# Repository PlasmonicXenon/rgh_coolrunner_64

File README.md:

# RGH_Coolrunner_64
This is an approximate replica of the coolrunner rev C based on the clones I 
have, but with a few extra features.

The extra features include solder points for level shifting post, an extra pll
io pad, as well as a crowbar point and a nand chip enable point for a potential
future Oban voltage glitch, if that ever happens and is ported to the xc2c64.

Note that the post points do not exactly match the configuration Octal450's 
level_shifter uses, which isn't a problem for my usecase.  If one wants to
use level_shifter, either edit the UCF file or wire to match it.

As mentioned above, this pcb has two IO pads that can drive the PLL point -- the
usual 3v3 io pad through a 22k resistor as usual, and an IO pad in the CPU VCCIO
bank. This second pad is only intended to be used with slims because the 
coolrunner  II's lowest IO voltage is 1.5V whereas phat CPUs use V_GPUCORE 
(~1.1 V) as their  IO voltage.  The intent here is that driving PLL_BYPASS with
a lower impedance should reduce its sensitivity to interference.

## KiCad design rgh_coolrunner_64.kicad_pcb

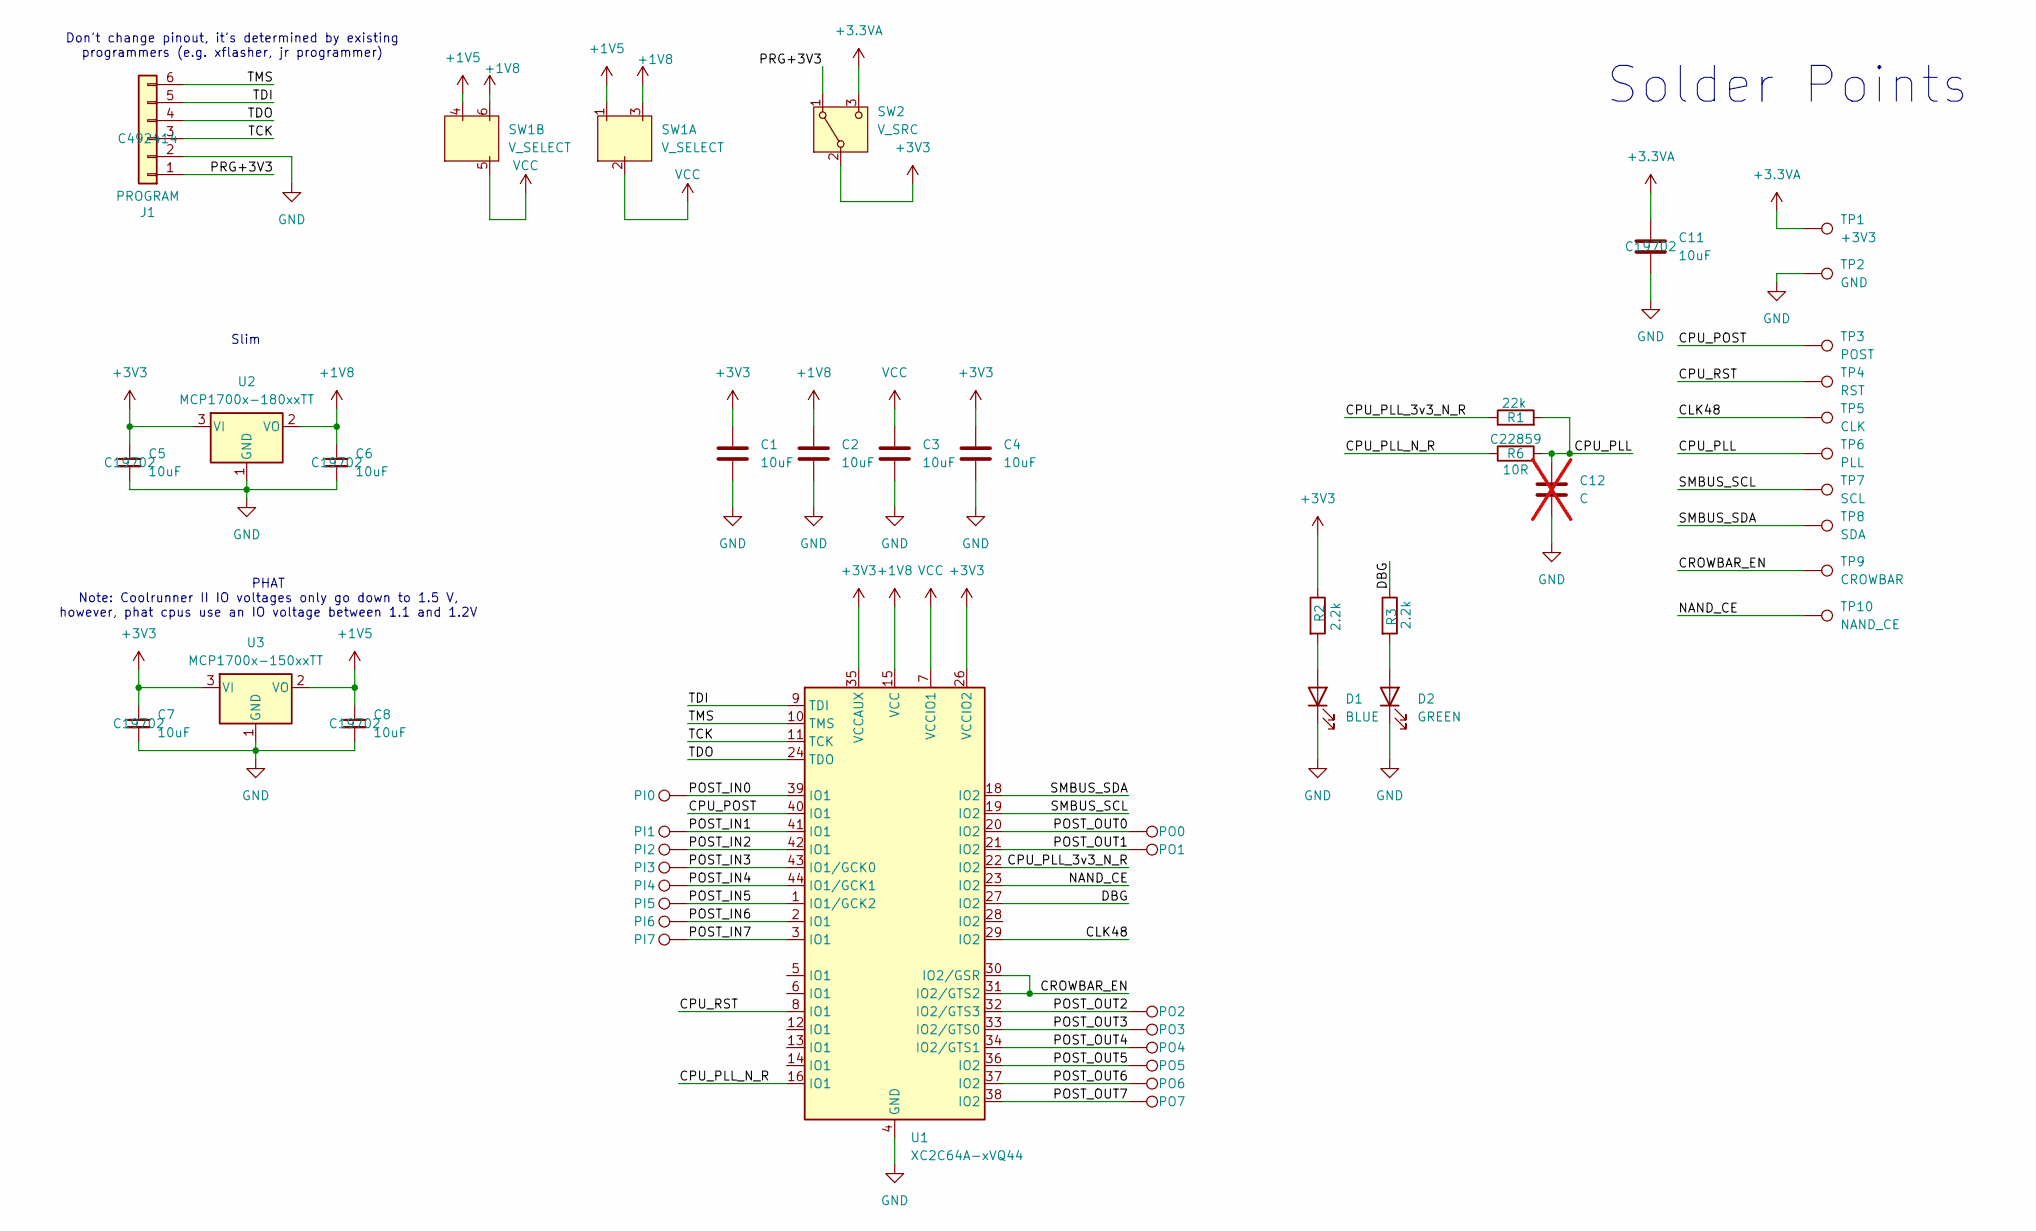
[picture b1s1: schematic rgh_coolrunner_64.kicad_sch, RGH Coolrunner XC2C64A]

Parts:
C1, C2, C3, C4: 10uF; C_0603_1608Metric
C5, C6, C7, C8, C11: 10uF; C_0603_1608Metric; LCSC Part # C19702
C12: C; C_0805_2012Metric_Pad1.18x1.45mm_HandSolder; not fitted
D1: BLUE; LED_0603_1608Metric; LCSC Part # C965807
D2: GREEN; LED_0603_1608Metric
J1: PROGRAM; PinHeader_1x06_P2.54mm_Horizontal; LCSC Part # C492414
PI0, PI1, PI2, PI3, PI4, PI5, PI6, PI7: TestPoint; TestPoint_Pad_D1.0mm
PO0, PO1, PO2, PO3, PO4, PO5, PO6, PO7: TestPoint; TestPoint_Pad_D1.0mm
R1: 22k; R_0603_1608Metric_Pad0.98x0.95mm_HandSolder
R2, R3: 2.2k; R_0603_1608Metric
R6: 10R; R_0603_1608Metric_Pad0.98x0.95mm_HandSolder; LCSC Part # C22859
SW1: V_SELECT; SW_DPDT_CK_JS202011JCQN
SW2: V_SRC; SW_SPDT_PCM12
TP1: +3V3; TestPoint_Pad_D2.0mm
TP2: GND; TestPoint_Pad_D2.0mm
TP3: POST; TestPoint_Pad_D2.0mm
TP4: RST; TestPoint_Pad_D2.0mm
TP5: CLK; TestPoint_Pad_D2.0mm
TP6: PLL; TestPoint_Pad_D2.0mm
TP7: SCL; TestPoint_Pad_D2.0mm
TP8: SDA; TestPoint_Pad_D2.0mm
TP9: CROWBAR; TestPoint_Pad_D2.0mm
TP10: NAND_CE; TestPoint_Pad_D2.0mm
U1: XC2C64A-xVQ44; TQFP-44_10x10mm_P0.8mm
U2: MCP1700x-180xxTT; SOT-23
U3: MCP1700x-150xxTT; SOT-23

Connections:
+1V5: C8.1, SW1.1 (A), SW1.4, U3.2 (VO)
+1V8: C2.1, C6.1, SW1.3 (C), SW1.6, U1.15 (VCC), U2.2 (VO)
+3.3VA: C11.1, SW2.3 (C), TP1.1
+3V3: C1.1, C4.1, C5.1, C7.1, R2.1, SW2.2 (B), U1.26 (VCCIO2), U1.35 (VCCAUX), U2.3 (VI), U3.3 (VI)
/CLK48: TP5.1, U1.29 (IO2)
/CPU_PLL: C12.1, R1.2, R6.2, TP6.1
/CPU_PLL_3v3_N_R: R1.1, U1.22 (IO2)
/CPU_PLL_N_R: R6.1, U1.16 (IO1)
/CPU_POST: TP3.1, U1.40 (IO1)
/CPU_RST: TP4.1, U1.8 (IO1)
/CROWBAR_EN: TP9.1, U1.30 (IO2/GSR), U1.31 (IO2/GTS2)
/DBG: R3.1, U1.27 (IO2)
/NAND_CE: TP10.1, U1.23 (IO2)
/POST_IN0: PI0.1, U1.39 (IO1)
/POST_IN1: PI1.1, U1.41 (IO1)
/POST_IN2: PI2.1, U1.42 (IO1)
/POST_IN3: PI3.1, U1.43 (IO1/GCK0)
/POST_IN4: PI4.1, U1.44 (IO1/GCK1)
/POST_IN5: PI5.1, U1.1 (IO1/GCK2)
/POST_IN6: PI6.1, U1.2 (IO1)
/POST_IN7: PI7.1, U1.3 (IO1)
/POST_OUT0: PO0.1, U1.20 (IO2)
/POST_OUT1: PO1.1, U1.21 (IO2)
/POST_OUT2: PO2.1, U1.32 (IO2/GTS3)
/POST_OUT3: PO3.1, U1.33 (IO2/GTS0)
/POST_OUT4: PO4.1, U1.34 (IO2/GTS1)
/POST_OUT5: PO5.1, U1.36 (IO2)
/POST_OUT6: PO6.1, U1.37 (IO2)
/POST_OUT7: PO7.1, U1.38 (IO2)
/PRG+3V3: J1.1, SW2.1 (A)
/SMBUS_SCL: TP7.1, U1.19 (IO2)
/SMBUS_SDA: TP8.1, U1.18 (IO2)
/TCK: J1.3, U1.11 (TCK)
/TDI: J1.5, U1.9 (TDI)
/TDO: J1.4, U1.24 (TDO)
/TMS: J1.6, U1.10 (TMS)
GND: C1.2, C2.2, C3.2, C4.2, C5.2, C6.2, C7.2, C8.2, C11.2, C12.2, D1.1 (K), D2.1 (K), J1.2, TP2.1, U1.4 (GND), U1.17 (GND), U1.25 (GND), U2.1 (GND), U3.1 (GND)
unnamed: D1.2 (A), R2.2
unnamed: D2.2 (A), R3.2
VCC: C3.1, SW1.2 (B), SW1.5, U1.7 (VCCIO1)

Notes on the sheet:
Slim
PHAT Note: Coolrunner II IO voltages only go down to 1.5 V, however, phat cpus use an IO voltage between 1.1 and 1.2V
Solder Points
Don't change pinout, it's determined by existing programmers (e.g. xflasher, jr programmer)

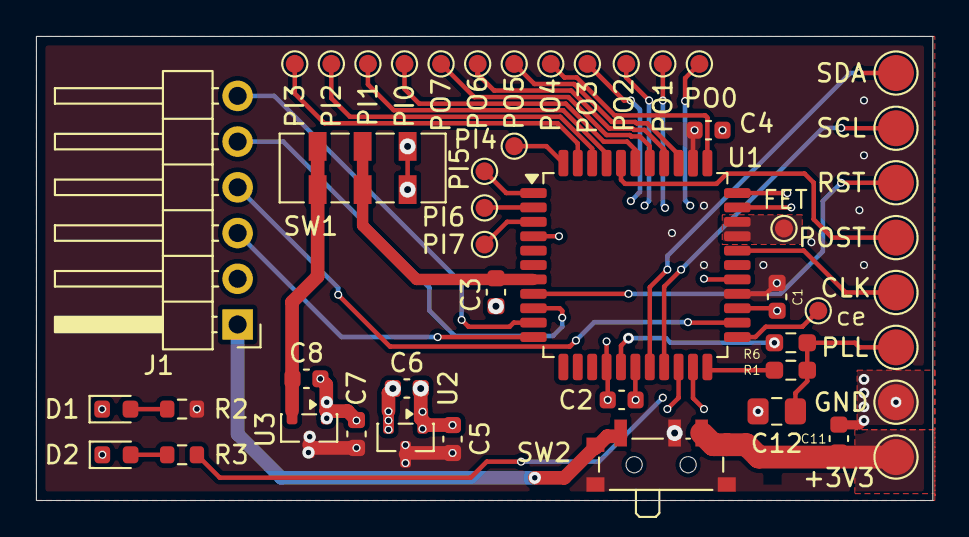
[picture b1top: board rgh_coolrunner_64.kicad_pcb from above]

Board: 4 copper layers, 49.8 x 25.8 mm, 48 parts (0 on the bottom side), 40 nets.

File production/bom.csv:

Designator,Footprint,Quantity,Value,LCSC Part #
"C1, C2, C3, C4",0603,4,C,
"C11, C5, C6, C7, C8",0603,5,10uF,C19702
D1,0603,1,BLUE,
D2,0603,1,GREEN,
J1,PinHeader_1x06_P2.54mm_Horizontal,1,PROGRAM,C492414
R1,0603,1,22k,C22859
"R2, R3",0603,2,2.2k,
R6,0603,1,10R,C22859
SW1,SW_SPDT_CK_JS102011SAQN,1,V_SELECT, C221660 
U1,TQFP-44_10x10mm_P0.8mm,1,XC2C64A-xVQ44,
U2,SOT-23,1,MCP1700x-180xxTT,
U3,SOT-23,1,MCP1700x-150xxTT,

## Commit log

2026-04-25 Initial commit of working design
